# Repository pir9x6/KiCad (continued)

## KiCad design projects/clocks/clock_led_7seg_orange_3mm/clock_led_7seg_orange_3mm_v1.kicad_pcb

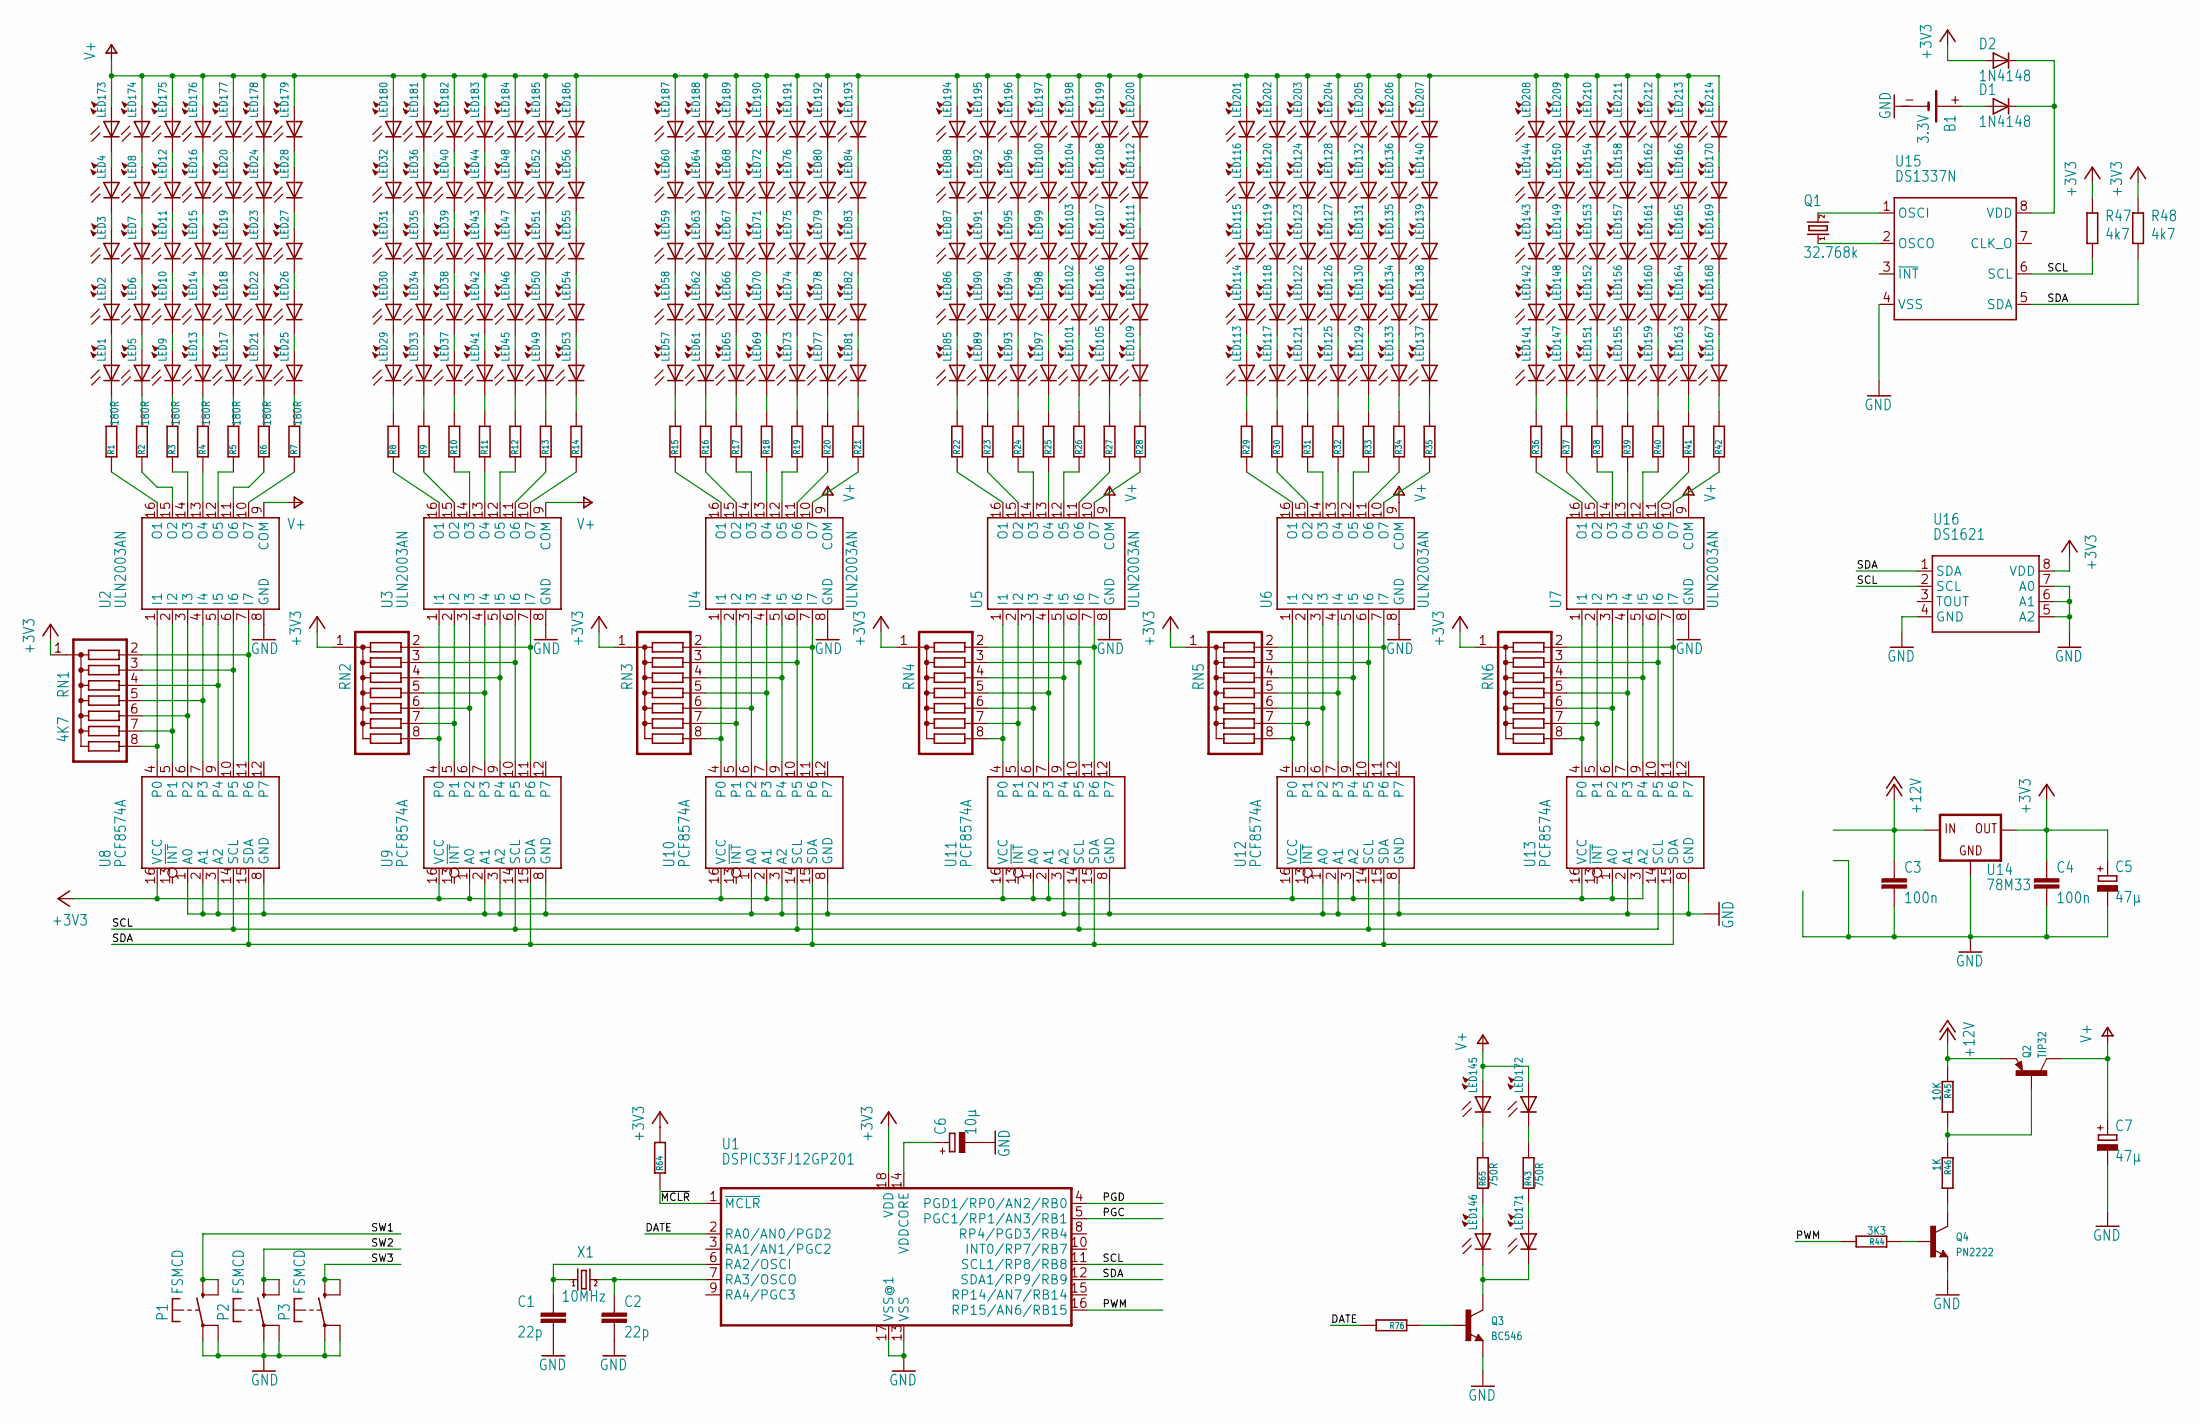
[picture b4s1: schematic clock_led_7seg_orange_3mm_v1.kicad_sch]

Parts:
B1: 3.3V; VITEC_TH
C1, C2: 22p; C025-025X050
C3, C4: 100n; C025-025X050
C5: 47µ; E2,5-5
C6: 10µ; E2,5-5
C7: 47µ; E2,5-5_HOR
D1, D2: 1N4148; DO35-5
LED1, LED2, LED3, LED4, LED5, LED6, LED7, LED8, LED9, LED10, LED11, LED12, LED13, LED14, LED15, LED16, LED17, LED18, LED19, LED20, LED21, LED22, LED23, LED24, LED25, LED26, LED27, LED28, LED29, LED30, LED31, LED32, LED33, LED34, LED35, LED36, LED37, LED38, LED39, LED40, LED41, LED42, LED43, LED44, LED45, LED46, LED47, LED48, LED49, LED50, LED51, LED52, LED53, LED54, LED55, LED56, LED57, LED58, LED59, LED60, LED61, LED62, LED63, LED64, LED65, LED66, LED67, LED68, LED69, LED70, LED71, LED72, LED73, LED74, LED75, LED76, LED77, LED78, LED79, LED80, LED81, LED82, LED83, LED84, LED85, LED86, LED87, LED88, LED89, LED90, LED91, LED92, LED93, LED94, LED95, LED96, LED97, LED98, LED99, LED100, LED101, LED102, LED103, LED104, LED105, LED106, LED107, LED108, LED109, LED110, LED111, LED112, LED113, LED114, LED115, LED116, LED117, LED118, LED119, LED120, LED121, LED122, LED123, LED124, LED125, LED126, LED127, LED128, LED129, LED130, LED131, LED132, LED133, LED134, LED135, LED136, LED137, LED138, LED139, LED140, LED141, LED142, LED143, LED144, LED145, LED146, LED147, LED148, LED149, LED150, LED151, LED152, LED153, LED154, LED155, LED156, LED157, LED158, LED159, LED160, LED161, LED162, LED163, LED164, LED165, LED166, LED167, LED168, LED169, LED170, LED171, LED172, LED173, LED174, LED175, LED176, LED177, LED178, LED179, LED180, LED181, LED182, LED183, LED184, LED185, LED186, LED187, LED188, LED189, LED190, LED191, LED192, LED193, LED194, LED195, LED196, LED197, LED198, LED199, LED200, LED201, LED202, LED203, LED204, LED205, LED206, LED207, LED208, LED209, LED210, LED211, LED212, LED213, LED214: LED3MM
P1, P2, P3: FSMCD
Q1: 32.768k; TC26H
Q2: TIP32; TO220
Q3: BC546; TO92-EBC
Q4: PN2222; TO92-CBE
R1, R2, R3, R4, R5, R6, R7: 180R; 0204_7
R8, R9, R10, R11, R12, R13, R14, R15, R16, R17, R18, R19, R20, R21, R22, R23, R24, R25, R26, R27, R28, R29, R30, R31, R32, R33, R34, R35, R36, R37, R38, R39, R40, R41, R42, R64: RESISTANCES0204/7; 0204_7
R43, R65: 750R; 0204_7
R44: 3K3; 0204_7
R45: 10K; 0204_7
R46: 1K; 0204_7
R47, R48: 4k7; 0204_7
R76: RESISTANCESR1206; R1206
RN1: 4K7; SIL8
RN2, RN3, RN4, RN5, RN6: G07R; SIL8
U1: DSPIC33FJ12GP201; DIP18
U2, U3: ULN2003AN; DIP16
U4, U5, U6, U7: ULN2003AN; DIL16
U8, U9, U10, U11, U12, U13: PCF8574A; DIP16
U14: 78M33; TO220L1
U15: DS1337N; DIP08
U16: DS1621; DIP08
X1: 10MHz; HC49U-V

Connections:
+3V3: C4.1, C5.+, D2.A, R47.P$2 (2), R48.P$2 (2), R64.P$2 (2), RN1.1, RN2.1, RN3.1, RN4.1, RN5.1, RN6.1, U1.18 (VDD), U8.16 (VCC), U9.1 (A0), U9.16 (VCC), U10.2 (A1), U10.16 (VCC), U11.1 (A0), U11.2 (A1), U11.16 (VCC), U12.3 (A2), U12.16 (VCC), U13.1 (A0), U13.3 (A2), U13.16 (VCC), U14.3 (OUT), U16.8 (VDD)
+12V: C3.1, Q2.3 (E), R45.P$1 (1), U14.1 (IN)
DATE: R76.2, U1.2 (RA0/AN0/PGD2)
GND: C1.2, C2.2, C3.2, C4.2, C5.-, C6.-, C7.-, P1.P$1, P1.P$2 (P@1), P2.P$1, P2.P$2 (P@1), P3.P$1, P3.P$2 (P@1), Q3.E, Q4.E, U1.13 (VSS), U1.17 (VSS@1), U2.8 (GND), U3.8 (GND), U4.8 (GND), U5.8 (GND), U6.8 (GND), U7.8 (GND), U8.1 (A0), U8.2 (A1), U8.3 (A2), U8.8 (GND), U9.2 (A1), U9.3 (A2), U9.8 (GND), U10.1 (A0), U10.3 (A2), U10.8 (GND), U11.3 (A2), U11.8 (GND), U12.1 (A0), U12.2 (A1), U12.8 (GND), U13.2 (A1), U13.8 (GND), U14.2 (GND), U15.4 (VSS), U16.4 (GND), U16.5 (A2), U16.6 (A1), U16.7 (A0)
unnamed: C2.1, U1.7 (RA3/OSCO), X1.2
unnamed: Q2.1 (B), R45.P$2 (2), R46.P$1 (1)
unnamed: LED146.K (C), LED171.K (C), Q3.C
unnamed: RN1.8, U2.1 (I1), U8.4 (P0)
unnamed: RN1.7, U2.2 (I2), U8.5 (P1)
unnamed: Q1.2, U15.1 (OSCI)
unnamed: Q1.1, U15.2 (OSCO)
unnamed: B1.+, D1.A
unnamed: RN1.6, U2.3 (I3), U8.6 (P2)
unnamed: RN1.5, U2.4 (I4), U8.7 (P3)
unnamed: RN1.4, U2.5 (I5), U8.9 (P4)
unnamed: RN1.3, U2.6 (I6), U8.10 (P5)
unnamed: RN1.2, U2.7 (I7), U8.11 (P6)
unnamed: R1.P$1 (1), U2.16 (O1)
unnamed: R2.P$1 (1), U2.15 (O2)
unnamed: R3.P$1 (1), U2.14 (O3)
unnamed: R4.P$1 (1), U2.13 (O4)
unnamed: R5.P$1 (1), U2.12 (O5)
unnamed: R6.P$1 (1), U2.11 (O6)
unnamed: R7.P$1 (1), U2.10 (O7)
unnamed: LED29.A, LED30.K (C)
unnamed: R8.P$1 (1), U3.16 (O1)
unnamed: R9.P$1 (1), U3.15 (O2)
unnamed: R10.P$1 (1), U3.14 (O3)
unnamed: R11.P$1 (1), U3.13 (O4)
unnamed: R12.P$1 (1), U3.12 (O5)
unnamed: R13.P$1 (1), U3.11 (O6)
unnamed: R14.P$1 (1), U3.10 (O7)
unnamed: R15.P$1 (1), U4.16 (O1)
unnamed: R16.P$1 (1), U4.15 (O2)
unnamed: R17.P$1 (1), U4.14 (O3)
unnamed: R18.P$1 (1), U4.13 (O4)
unnamed: R19.P$1 (1), U4.12 (O5)
unnamed: R20.P$1 (1), U4.11 (O6)
unnamed: R21.P$1 (1), U4.10 (O7)
unnamed: R22.P$1 (1), U5.16 (O1)
unnamed: R23.P$1 (1), U5.15 (O2)
unnamed: R24.P$1 (1), U5.14 (O3)
unnamed: R25.P$1 (1), U5.13 (O4)
unnamed: Q4.C, R46.P$2 (2)
unnamed: R26.P$1 (1), U5.12 (O5)
unnamed: R27.P$1 (1), U5.11 (O6)
unnamed: Q4.B, R44.P$1 (1)
unnamed: C1.1, U1.6 (RA2/OSCI), X1.1
unnamed: R28.P$1 (1), U5.10 (O7)
unnamed: R29.P$1 (1), U6.16 (O1)
unnamed: R30.P$1 (1), U6.15 (O2)
unnamed: R31.P$1 (1), U6.14 (O3)
unnamed: R32.P$1 (1), U6.13 (O4)
unnamed: LED1.K (C), R1.P$2 (2)
unnamed: LED1.A, LED2.K (C)
unnamed: LED2.A, LED3.K (C)
unnamed: LED3.A, LED4.K (C)
unnamed: LED5.K (C), R2.P$2 (2)
unnamed: LED5.A, LED6.K (C)
unnamed: LED6.A, LED7.K (C)
unnamed: LED7.A, LED8.K (C)
unnamed: LED9.A, LED10.K (C)
unnamed: LED10.A, LED11.K (C)
unnamed: LED11.A, LED12.K (C)
unnamed: LED13.A, LED14.K (C)
unnamed: LED14.A, LED15.K (C)
unnamed: LED15.A, LED16.K (C)
unnamed: LED17.A, LED18.K (C)
unnamed: LED18.A, LED19.K (C)
unnamed: LED19.A, LED20.K (C)
unnamed: LED21.A, LED22.K (C)
unnamed: LED22.A, LED23.K (C)
unnamed: LED23.A, LED24.K (C)
unnamed: LED25.A, LED26.K (C)
unnamed: LED26.A, LED27.K (C)
unnamed: LED27.A, LED28.K (C)
unnamed: LED30.A, LED31.K (C)
unnamed: LED31.A, LED32.K (C)
unnamed: LED33.A, LED34.K (C)
unnamed: LED34.A, LED35.K (C)
unnamed: LED35.A, LED36.K (C)
unnamed: LED37.A, LED38.K (C)
unnamed: LED38.A, LED39.K (C)
unnamed: LED39.A, LED40.K (C)
unnamed: LED41.A, LED42.K (C)
unnamed: LED42.A, LED43.K (C)
unnamed: LED43.A, LED44.K (C)
unnamed: LED45.A, LED46.K (C)
unnamed: LED46.A, LED47.K (C)
unnamed: LED47.A, LED48.K (C)
unnamed: LED49.A, LED50.K (C)
unnamed: LED50.A, LED51.K (C)
unnamed: LED51.A, LED52.K (C)
unnamed: LED53.A, LED54.K (C)
unnamed: LED54.A, LED55.K (C)
unnamed: LED55.A, LED56.K (C)
unnamed: LED57.A, LED58.K (C)
unnamed: LED58.A, LED59.K (C)
unnamed: LED59.A, LED60.K (C)
unnamed: LED61.A, LED62.K (C)
unnamed: LED62.A, LED63.K (C)
unnamed: LED63.A, LED64.K (C)
unnamed: LED65.A, LED66.K (C)
unnamed: LED66.A, LED67.K (C)
unnamed: LED67.A, LED68.K (C)
unnamed: LED69.A, LED70.K (C)
unnamed: LED70.A, LED71.K (C)
unnamed: LED71.A, LED72.K (C)
unnamed: LED73.A, LED74.K (C)
unnamed: LED74.A, LED75.K (C)
unnamed: LED75.A, LED76.K (C)
unnamed: LED77.A, LED78.K (C)
unnamed: LED78.A, LED79.K (C)
unnamed: LED79.A, LED80.K (C)
unnamed: LED81.A, LED82.K (C)
unnamed: LED82.A, LED83.K (C)
unnamed: LED83.A, LED84.K (C)
unnamed: LED85.A, LED86.K (C)
unnamed: LED86.A, LED87.K (C)
unnamed: LED87.A, LED88.K (C)
unnamed: LED89.A, LED90.K (C)
unnamed: LED90.A, LED91.K (C)
unnamed: LED91.A, LED92.K (C)
unnamed: LED93.A, LED94.K (C)
unnamed: LED94.A, LED95.K (C)
unnamed: LED95.A, LED96.K (C)
unnamed: LED97.A, LED98.K (C)
unnamed: LED98.A, LED99.K (C)
unnamed: LED99.A, LED100.K (C)
unnamed: LED101.A, LED102.K (C)
unnamed: LED102.A, LED103.K (C)
unnamed: LED103.A, LED104.K (C)
unnamed: LED105.A, LED106.K (C)
unnamed: LED106.A, LED107.K (C)
unnamed: LED107.A, LED108.K (C)
unnamed: LED109.A, LED110.K (C)
unnamed: LED110.A, LED111.K (C)
unnamed: LED111.A, LED112.K (C)
unnamed: LED113.A, LED114.K (C)
unnamed: LED114.A, LED115.K (C)
unnamed: LED115.A, LED116.K (C)
unnamed: LED117.A, LED118.K (C)
unnamed: LED118.A, LED119.K (C)
unnamed: LED119.A, LED120.K (C)
unnamed: LED121.A, LED122.K (C)
unnamed: LED122.A, LED123.K (C)
unnamed: LED123.A, LED124.K (C)
unnamed: LED125.A, LED126.K (C)
unnamed: LED126.A, LED127.K (C)
unnamed: LED127.A, LED128.K (C)
unnamed: LED129.A, LED130.K (C)
unnamed: LED130.A, LED131.K (C)
unnamed: LED131.A, LED132.K (C)
unnamed: LED133.A, LED134.K (C)
unnamed: LED134.A, LED135.K (C)
unnamed: LED135.A, LED136.K (C)
unnamed: LED137.A, LED138.K (C)
unnamed: LED138.A, LED139.K (C)
unnamed: LED139.A, LED140.K (C)
unnamed: LED141.A, LED142.K (C)
unnamed: LED142.A, LED143.K (C)
unnamed: LED143.A, LED144.K (C)
unnamed: LED147.A, LED148.K (C)
unnamed: LED148.A, LED149.K (C)
unnamed: LED149.A, LED150.K (C)
unnamed: LED151.A, LED152.K (C)
unnamed: LED152.A, LED153.K (C)
unnamed: LED153.A, LED154.K (C)
unnamed: LED155.A, LED156.K (C)
unnamed: LED156.A, LED157.K (C)
unnamed: LED157.A, LED158.K (C)
unnamed: LED159.A, LED160.K (C)
unnamed: LED160.A, LED161.K (C)
unnamed: LED161.A, LED162.K (C)
unnamed: LED163.A, LED164.K (C)
unnamed: LED164.A, LED165.K (C)
unnamed: LED165.A, LED166.K (C)
unnamed: LED167.A, LED168.K (C)
unnamed: LED168.A, LED169.K (C)
unnamed: LED169.A, LED170.K (C)
unnamed: LED146.A, R65.P$1 (1)
unnamed: LED171.A, R43.P$1 (1)
unnamed: LED9.K (C), R3.P$2 (2)
unnamed: LED13.K (C), R4.P$2 (2)
unnamed: LED17.K (C), R5.P$2 (2)
unnamed: LED21.K (C), R6.P$2 (2)
unnamed: LED25.K (C), R7.P$2 (2)
unnamed: LED29.K (C), R8.P$2 (2)
unnamed: LED33.K (C), R9.P$2 (2)
unnamed: LED37.K (C), R10.P$2 (2)
unnamed: LED41.K (C), R11.P$2 (2)
unnamed: LED45.K (C), R12.P$2 (2)
unnamed: LED49.K (C), R13.P$2 (2)
unnamed: LED53.K (C), R14.P$2 (2)
unnamed: LED57.K (C), R15.P$2 (2)
unnamed: LED61.K (C), R16.P$2 (2)
unnamed: LED65.K (C), R17.P$2 (2)
unnamed: LED69.K (C), R18.P$2 (2)
unnamed: LED73.K (C), R19.P$2 (2)
unnamed: LED77.K (C), R20.P$2 (2)
unnamed: LED81.K (C), R21.P$2 (2)
unnamed: LED85.K (C), R22.P$2 (2)
unnamed: LED89.K (C), R23.P$2 (2)
unnamed: LED93.K (C), R24.P$2 (2)
unnamed: LED97.K (C), R25.P$2 (2)
unnamed: LED101.K (C), R26.P$2 (2)
unnamed: LED105.K (C), R27.P$2 (2)
unnamed: LED109.K (C), R28.P$2 (2)
unnamed: LED113.K (C), R29.P$2 (2)
unnamed: LED117.K (C), R30.P$2 (2)
unnamed: LED121.K (C), R31.P$2 (2)
unnamed: LED125.K (C), R32.P$2 (2)
unnamed: LED129.K (C), R33.P$2 (2)
unnamed: LED133.K (C), R34.P$2 (2)
unnamed: LED137.K (C), R35.P$2 (2)
unnamed: LED141.K (C), R36.P$2 (2)
unnamed: LED147.K (C), R37.P$2 (2)
unnamed: LED151.K (C), R38.P$2 (2)
unnamed: LED172.K (C), R43.P$2 (2)
unnamed: LED155.K (C), R39.P$2 (2)
unnamed: LED159.K (C), R40.P$2 (2)
unnamed: LED163.K (C), R41.P$2 (2)
unnamed: LED167.K (C), R42.P$2 (2)
unnamed: R33.P$1 (1), U6.12 (O5)
unnamed: R34.P$1 (1), U6.11 (O6)
unnamed: R35.P$1 (1), U6.10 (O7)
unnamed: LED145.K (C), R65.P$2 (2)
unnamed: R36.P$1 (1), U7.16 (O1)
unnamed: R37.P$1 (1), U7.15 (O2)
unnamed: Q3.B, R76.1
unnamed: R38.P$1 (1), U7.14 (O3)
unnamed: R39.P$1 (1), U7.13 (O4)
unnamed: R40.P$1 (1), U7.12 (O5)
unnamed: R41.P$1 (1), U7.11 (O6)
unnamed: R42.P$1 (1), U7.10 (O7)
unnamed: RN2.8, U3.1 (I1), U9.4 (P0)
unnamed: RN2.7, U3.2 (I2), U9.5 (P1)
unnamed: RN2.6, U3.3 (I3), U9.6 (P2)
unnamed: RN2.5, U3.4 (I4), U9.7 (P3)
unnamed: RN2.4, U3.5 (I5), U9.9 (P4)
unnamed: RN2.3, U3.6 (I6), U9.10 (P5)
unnamed: RN2.2, U3.7 (I7), U9.11 (P6)
unnamed: C6.+, U1.14 (VDDCORE)
unnamed: RN3.8, U4.1 (I1), U10.4 (P0)
unnamed: RN3.7, U4.2 (I2), U10.5 (P1)
unnamed: RN3.6, U4.3 (I3), U10.6 (P2)
unnamed: RN3.5, U4.4 (I4), U10.7 (P3)
unnamed: RN3.4, U4.5 (I5), U10.9 (P4)
unnamed: RN3.3, U4.6 (I6), U10.10 (P5)
unnamed: RN3.2, U4.7 (I7), U10.11 (P6)
unnamed: RN4.8, U5.1 (I1), U11.4 (P0)
unnamed: RN4.7, U5.2 (I2), U11.5 (P1)
unnamed: RN4.6, U5.3 (I3), U11.6 (P2)
unnamed: RN4.5, U5.4 (I4), U11.7 (P3)
unnamed: RN4.4, U5.5 (I5), U11.9 (P4)
unnamed: RN4.3, U5.6 (I6), U11.10 (P5)
unnamed: RN4.2, U5.7 (I7), U11.11 (P6)
unnamed: RN5.8, U6.1 (I1), U12.4 (P0)
unnamed: RN5.7, U6.2 (I2), U12.5 (P1)
unnamed: RN5.6, U6.3 (I3), U12.6 (P2)
unnamed: RN5.5, U6.4 (I4), U12.7 (P3)
unnamed: RN5.4, U6.5 (I5), U12.9 (P4)
unnamed: RN5.3, U6.6 (I6), U12.10 (P5)
unnamed: RN5.2, U6.7 (I7), U12.11 (P6)
unnamed: RN6.8, U7.1 (I1), U13.4 (P0)
unnamed: RN6.7, U7.2 (I2), U13.5 (P1)
unnamed: RN6.6, U7.3 (I3), U13.6 (P2)
unnamed: RN6.5, U7.4 (I4), U13.7 (P3)
unnamed: RN6.4, U7.5 (I5), U13.9 (P4)
unnamed: RN6.3, U7.6 (I6), U13.10 (P5)
unnamed: RN6.2, U7.7 (I7), U13.11 (P6)
unnamed: D1.K (C), D2.K (C), U15.8 (VDD)
unnamed: LED4.A, LED173.K (C)
unnamed: LED8.A, LED174.K (C)
unnamed: LED12.A, LED175.K (C)
unnamed: LED16.A, LED176.K (C)
unnamed: LED20.A, LED177.K (C)
unnamed: LED24.A, LED178.K (C)
unnamed: LED28.A, LED179.K (C)
unnamed: LED32.A, LED180.K (C)
unnamed: LED36.A, LED181.K (C)
unnamed: LED40.A, LED182.K (C)
unnamed: LED44.A, LED183.K (C)
unnamed: LED48.A, LED184.K (C)
unnamed: LED52.A, LED185.K (C)
unnamed: LED56.A, LED186.K (C)
unnamed: LED60.A, LED187.K (C)
unnamed: LED64.A, LED188.K (C)
unnamed: LED68.A, LED189.K (C)
unnamed: LED72.A, LED190.K (C)
unnamed: LED76.A, LED191.K (C)
unnamed: LED80.A, LED192.K (C)
unnamed: LED84.A, LED193.K (C)
unnamed: LED88.A, LED194.K (C)
unnamed: LED92.A, LED195.K (C)
unnamed: LED96.A, LED196.K (C)
unnamed: LED100.A, LED197.K (C)
unnamed: LED104.A, LED198.K (C)
unnamed: LED108.A, LED199.K (C)
unnamed: LED112.A, LED200.K (C)
unnamed: LED116.A, LED201.K (C)
unnamed: LED120.A, LED202.K (C)
unnamed: LED124.A, LED203.K (C)
unnamed: LED128.A, LED204.K (C)
unnamed: LED132.A, LED205.K (C)
unnamed: LED136.A, LED206.K (C)
unnamed: LED140.A, LED207.K (C)
unnamed: LED144.A, LED208.K (C)
unnamed: LED150.A, LED209.K (C)
unnamed: LED154.A, LED210.K (C)
unnamed: LED158.A, LED211.K (C)
unnamed: LED162.A, LED212.K (C)
unnamed: LED166.A, LED213.K (C)
unnamed: LED170.A, LED214.K (C)
PGC: U1.5 (PGC1/RP1/AN3/RB1)
PGD: U1.4 (PGD1/RP0/AN2/RB0)
PWM: R44.P$2 (2), U1.16 (RP15/AN6/RB15)
SCL: R47.P$1 (1), U1.11 (SCL1/RP8/RB8), U8.14 (SCL), U9.14 (SCL), U10.14 (SCL), U11.14 (SCL), U12.14 (SCL), U13.14 (SCL), U15.6 (SCL), U16.2 (SCL)
SDA: R48.P$1 (1), U1.12 (SDA1/RP9/RB9), U8.15 (SDA), U9.15 (SDA), U10.15 (SDA), U11.15 (SDA), U12.15 (SDA), U13.15 (SDA), U15.5 (SDA), U16.1 (SDA)
SW1: P1.P$3 (S), P1.P$4 (S@1)
SW2: P2.P$3 (S), P2.P$4 (S@1)
SW3: P3.P$3 (S), P3.P$4 (S@1)
V+: C7.+, LED145.A, LED172.A, LED173.A, LED174.A, LED175.A, LED176.A, LED177.A, LED178.A, LED179.A, LED180.A, LED181.A, LED182.A, LED183.A, LED184.A, LED185.A, LED186.A, LED187.A, LED188.A, LED189.A, LED190.A, LED191.A, LED192.A, LED193.A, LED194.A, LED195.A, LED196.A, LED197.A, LED198.A, LED199.A, LED200.A, LED201.A, LED202.A, LED203.A, LED204.A, LED205.A, LED206.A, LED207.A, LED208.A, LED209.A, LED210.A, LED211.A, LED212.A, LED213.A, LED214.A, Q2.2 (C), U2.9 (COM), U3.9 (COM), U4.9 (COM), U5.9 (COM), U6.9 (COM), U7.9 (COM)
~MCLR: R64.P$1 (1), U1.1 (~MCLR)

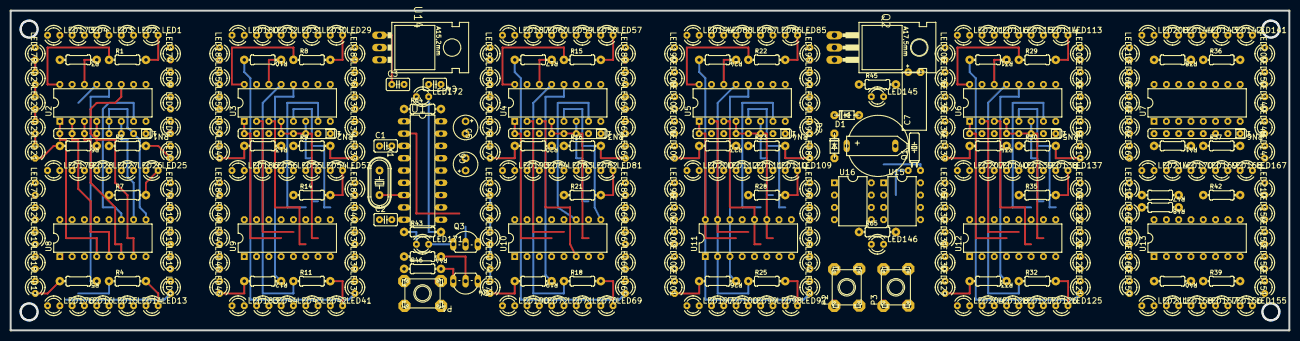
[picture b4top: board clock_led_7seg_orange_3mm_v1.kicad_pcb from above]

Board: 16 copper layers, 264.2 x 66.0 mm, 305 parts (1 on the bottom side), 322 nets.

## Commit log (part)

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2025-05-02 added subfolders
2026-06-21 remove .bak files
